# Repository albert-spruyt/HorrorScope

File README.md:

# HorrorScope / ScaCheapier

This repository contains all the firmware source, scripts and notebooks for the ScaCheapier workshop given at 35c3. 

We gave a talk about this work at Troopers 2019 NGI, with a different perspective. You can find the slides in the presentation directory.

## Abstract 
From: https://events.ccc.de/congress/2018/wiki/index.php/Session:ScaCheapier

Want to recover cryptographic keys by just looking at a chip's power usage, for the price of a few beers?

In this workshop we will show you how to break AES with just ~5 euro of equipment (plus your laptop and a bit of code).

Following in the tradition of the ChipWhisperer, but with even cheaper hardware, come and join the world of hardware side channel attacks. With a simple custom PCB (schematics provided), a cheap off-the-shelf MCU and a handful of supporting components, you'll have no problem stealing the keys. 

## Presentation

During the workshop we partially re-used a presentation created by Ilya Kizhvatov. The original slides can be found here:  
https://www.slideshare.net/phdays/ss-35302416  
A recording of Ilya himself giving the talk can be found here: https://vimeo.com/100108647  

If you saw our talk at Troopers, you missed out on all the theory; you can watch Ilya's presentation to get it!

## Code repository

The code in the repository, in particular the FI and Scope FW parts, should be considered PoC code. In fact, don't take anything here too seriously. Have fun!

The repository is organized as follows:

Scope   - Scope and Glitcher Firmware (firmware in lufa\*/Projects/HorrorScope  
Acq     - Python acquisition scripts including the Scope GUI  
FI      - Python FI scripts/ including plotting  
julia   - The julia jupyter notebook  
presentation - The presentation for the workshop (and the troopers talk) 
PCB     - PCB files  

#### Patched LUFA
The Scope folder contains an entire copy of LUFA http://fourwalledcubicle.com/LUFA.php  

To maximize the amount of SRAM available as sample memory LUFA has been patched to minimize the number and size of USB buffers.   

The patch has been applied in Drivers/USB/Core/XMEGA/Endpoint_XMEGA.h  

## Installation

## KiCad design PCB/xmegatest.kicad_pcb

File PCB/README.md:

# HorrorScope PCB design

These are the kicad source files for our 'horrorscope' PCB. You can find gerbers in the 'horrorscope' directory.

(The 'breakout' directory contains gerbers for the breakout PCB we developed for debugging, which may be interesting too.)

Obviously .. we are not electrical engineers. Or good at PCB design. But it works! :)

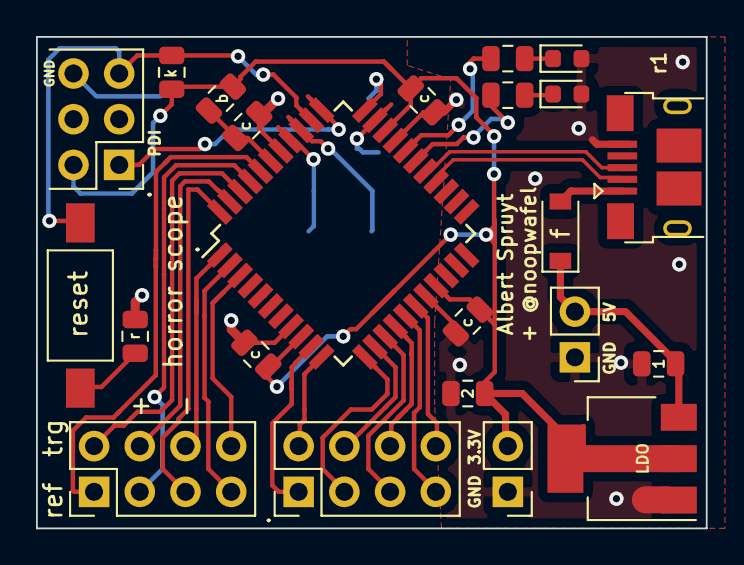
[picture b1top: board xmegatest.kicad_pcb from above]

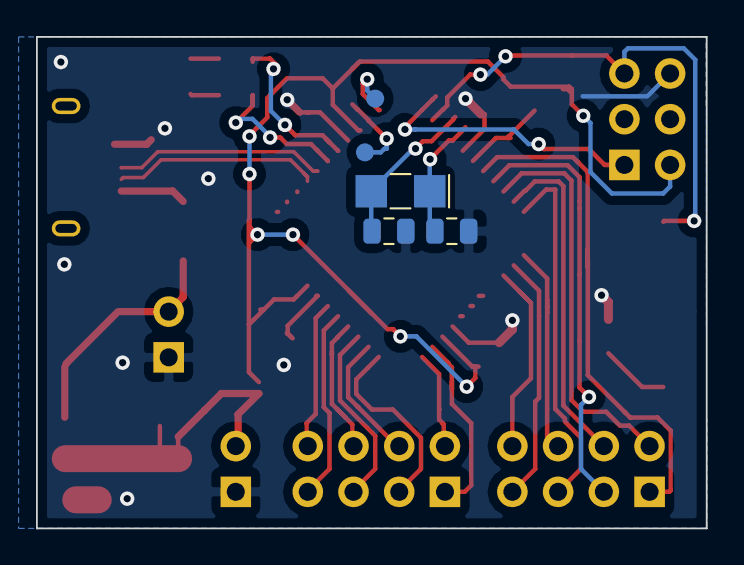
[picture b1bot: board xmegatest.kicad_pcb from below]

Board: 2 copper layers, 37.2 x 27.3 mm, 25 parts (3 on the bottom side), 30 nets.

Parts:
C1, C3: C_Small; C_0805_2012Metric
C2, C4: 100uF; C_0805_2012Metric
C5, C6, C7, C11: 100nF; C_0805_2012Metric
F1: fuse; D_SOD-123
J1: AVR-PDI-6; PinHeader_2x03_P2.54mm_Vertical_noline
J2: USB_B_Micro; USB_Micro-B_Amphenol_hax
J5, J7: Conn_01x08_Female; PinHeader_2x04_P2.54mm_Vertical
JP1: 0; PinHeader_1x02_P2.54mm_Vertical
L1: Ferrite_Bead_Small; L_0805_2012Metric
LED1, LED2: LED_0603_1608Metric
R1: 10k; R_0805_2012Metric
R2: 0; R_0805_2012Metric
RLED1, RLED2: R_0805_2012Metric
SW1: SW_Push; SW_SPST_FSMSM
U1: LM1117-3.3; SOT-223-3_TabPin2
U2: ATxmega128A4U-AU; TQFP-44_10x10mm_P0.8mm
Y1: 32.768hz; Crystal_SMD_MicroCrystal_CC7V-T1A-2Pin_3.2x1.5mm_HandSolder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

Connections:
+3V3: C4.1, C5.2, C6.2, C11.2, J1.2, JP1.2, L1.2, R1.1, U1.2, U2.9, U2.19, U2.31
+5V: C2.1, F1.1, U1.3
/PDI_DATA: J1.1, U2.34
/RESET: J1.5, R1.2, SW1.2, U2.35
/USBD+: J2.3, U2.27
/USBD-: J2.2, U2.26
/XTAL1: C1.1, U2.37, Y1.1
/XTAL2: C3.1, U2.36, Y1.2
GND: C1.2, C2.2, C3.2, C4.2, C5.1, C6.1, C7.1, C11.1, J1.6, J2.5, JP1.1, LED1.2, LED2.2, R2.1, U1.1, U2.8, U2.18, U2.30, U2.38
unnamed: C7.2, L1.1, U2.39
unnamed: F1.2, J2.1
unnamed: J5.1, U2.40
unnamed: J5.3, U2.41
unnamed: J5.2, U2.42
unnamed: J5.4, U2.43
unnamed: J5.5, U2.44
unnamed: J5.6, U2.1
unnamed: J5.7, U2.2
unnamed: J5.8, U2.3
unnamed: J7.1, U2.10
unnamed: J7.2, U2.11
unnamed: J7.3, U2.12
unnamed: J7.4, U2.13
unnamed: J7.5, U2.14
unnamed: J7.6, U2.15
unnamed: J7.7, U2.16
unnamed: J7.8, U2.17
unnamed: R2.2, SW1.1
unnamed: RLED2.1, U2.28
unnamed: RLED1.1, U2.29

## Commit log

2019-01-07 Initial commit after the 35c3 workshops
2019-01-07 Cleaned up the markdown
2019-03-16 add PCB, update README
2019-03-19 add presentation from troopers
2019-12-24 Fixed bit-rot: horrorscope not building Added a auto-feature for the gui
